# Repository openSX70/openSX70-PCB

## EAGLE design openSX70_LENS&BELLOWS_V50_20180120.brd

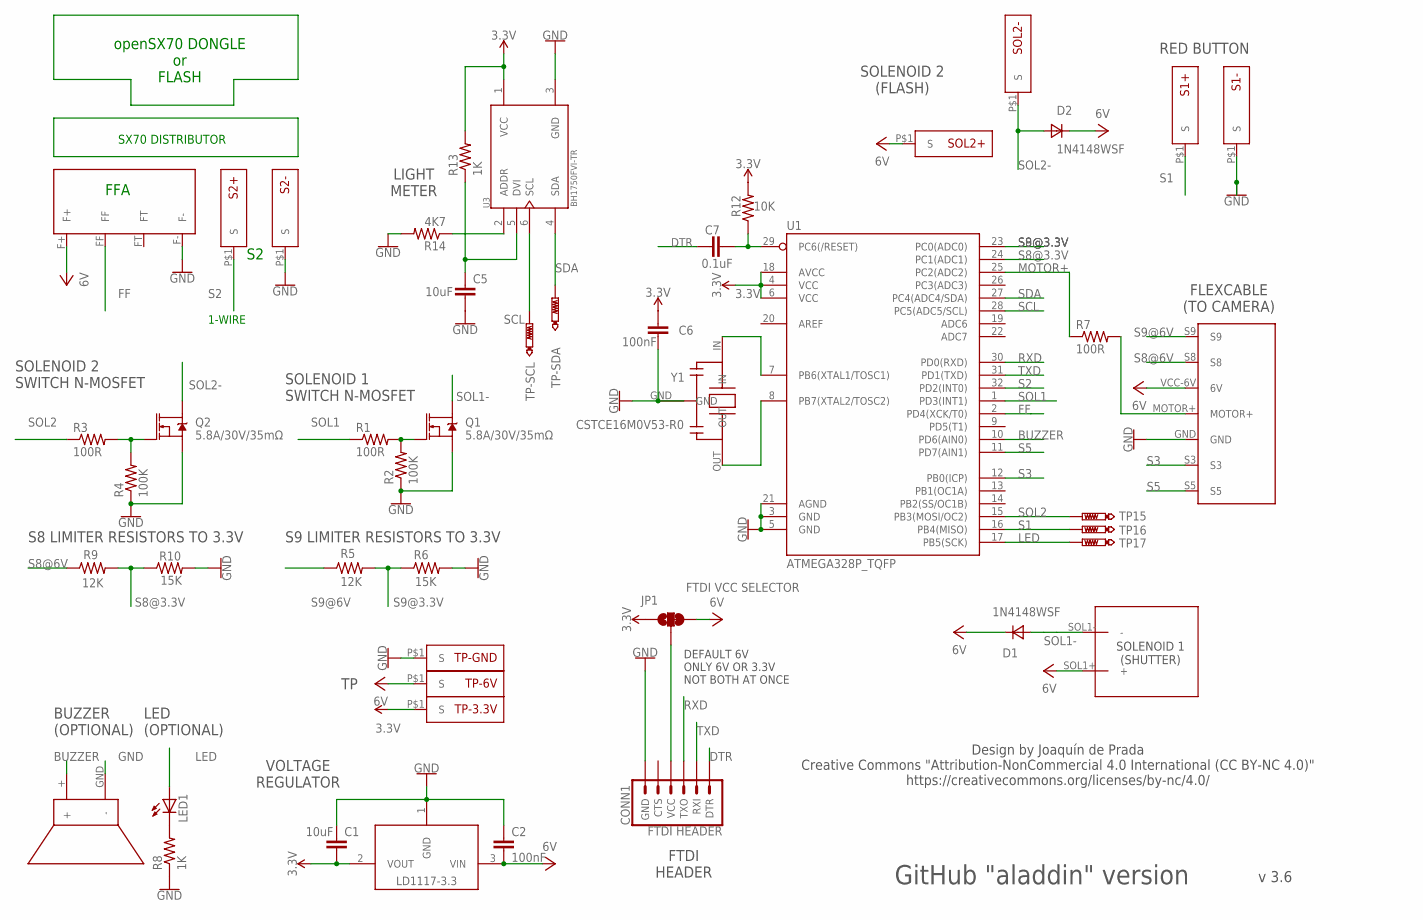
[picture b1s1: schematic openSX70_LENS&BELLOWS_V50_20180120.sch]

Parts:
BUZZ1: CSET8-5G; CSET8-5G_PACKAGE
C1, C5: 10uF; 0603
C2, C6: 100nF; C0603K
C7: 0.1uF; 0603
CONN1: FTDI HEADER; 1X06
D1, D2: 1N4148WSF; SOD323
JP1: FTDI VCC SELECTOR; SMT-JUMPER_3_1-NC_TRACE_SILK
LD11173.3V: LD1117 3.3V; SOT223
LED1: LEDCHIPLED_0805; CHIPLED_0805
Q1, Q2: 5.8A/30V/35mΩ; SOT23-3
R1, R3, R7: 100R; R0603
R2, R4: 100K; R0603
R5, R9: 12K; R0603
R6, R10: 15K; R0603
R8, R13: 1K; R0603
R12: 10K; R0603
R14: 4K7; R0603
S1+, S1-, S2+, S2-: SX70-S-PAD-NEW; SX70-S-PAD2
SOL1: SX70-SOLENOID1-2PADS; SX70-SOLENOID1-2
SOL2+, SOL2-: SX70-S-PAD-NEW; SX70-S-PAD2
TP15, TP16, TP17: PTR1TP08R; TP08R
TP-3.3V, TP-6V: SX70-S-PAD-NEW; SX70-S-PAD2
TP-GND: SX70-S-PAD-NEW; SX70-S-PAD2
TP-SCL: PTR1TP08R; TP08R
TP-SDA: PTR1TP08R; TP08R
U1: ATMEGA328P_TQFP; TQFP32-08
U3: BH1750FVI-TR; SOTFL50P300X75-6N
U$1: SX70-7-PAD
U$2: FFA; FFA-PAD-PACKAGE
Y1: CSTCE16M0V53-R0; CFP95P160X100-3N

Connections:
3.3V: C1.2, C6.1, JP1.1, LD11173.3V.2 (VOUT), R12.2, R13.2, TP-3.3V.P$1, U1.4 (VCC), U1.6 (VCC), U1.18 (AVCC), U3.1 (VCC)
6V: C2.2, D1.1 (C), D2.1 (C), JP1.3, LD11173.3V.3 (VIN), SOL1.SOL1+ (+), SOL2+.P$1, TP-6V.P$1, U$1.VCC-6V (6V), U$2.F+
BUZZER: BUZZ1.+, U1.10 (PD6(AIN0))
DTR: C7.1, CONN1.1 (DTR)
FF: U1.2 (PD4(XCK/T0)), U$2.FF
GND: BUZZ1.GND (-), C1.1, C2.1, C5.2, C6.2, CONN1.6 (GND), LD11173.3V.1 (GND), Q1.2 (S), Q2.2 (S), R2.1, R4.1, R6.2, R8.1, R10.2, R14.2, S1-.P$1, S2-.P$1, TP-GND.P$1, U1.3 (GND), U1.5 (GND), U1.21 (AGND), U3.3 (GND), U$1.GND, U$2.F-, Y1.GND
LED: LED1.A, TP17.TP, U1.17 (PB5(SCK))
MOTOR+: R7.1, U1.25 (PC2(ADC2))
MOTOR-HEADER: R7.2, U$1.MOTOR+
unnamed: Q1.1 (G), R1.2, R2.2
unnamed: C5.1, R13.1, U3.5 (DVI)
unnamed: Q2.1 (G), R3.2, R4.2
unnamed: U1.7 (PB6(XTAL1/TOSC1)), Y1.IN
unnamed: LED1.C, R8.2
unnamed: U1.8 (PB7(XTAL2/TOSC2)), Y1.OUT
unnamed: C7.2, R12.1, U1.29 (PC6(/RESET))
unnamed: R14.1, U3.2 (ADDR)
unnamed: CONN1.4 (VCC), JP1.2
RXD: CONN1.3 (TXO), U1.30 (PD0(RXD))
S1: S1+.P$1, TP16.TP, U1.16 (PB4(MISO))
S2: S2+.P$1, U1.32 (PD2(INT0))
S3: U1.12 (PB0(ICP)), U$1.S3
S5: U1.11 (PD7(AIN1)), U$1.S5
S8@3.3V: R9.2, R10.1, U1.24 (PC1(ADC1))
S8@6V: R9.1, U$1.S8
S9@3.3V: R5.2, R6.1, U1.23 (PC0(ADC0))
S9@6V: R5.1, U$1.S9
SCL: TP-SCL.TP, U1.28 (PC5(ADC5/SCL)), U3.6 (SCL)
SDA: TP-SDA.TP, U1.27 (PC4(ADC4/SDA)), U3.4 (SDA)
SOL1: R1.1, U1.1 (PD3(INT1))
SOL1-: D1.2 (A), Q1.3 (D), SOL1.SOL1- (-)
SOL2: R3.1, TP15.TP, U1.15 (PB3(MOSI/OC2))
SOL2-: D2.2 (A), Q2.3 (D), SOL2-.P$1
TXD: CONN1.2 (RXI), U1.31 (PD1(TXD))

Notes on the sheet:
1-WIRE
FFA
LIGHT METER
FLEXCABLE (TO CAMERA)
RED BUTTON
SOLENOID 1 (SHUTTER)
SOLENOID 2 (FLASH)
FTDI HEADER
VOLTAGE REGULATOR
BUZZER (OPTIONAL)
LED (OPTIONAL)
S8 LIMITER RESISTORS TO 3.3V
S9 LIMITER RESISTORS TO 3.3V
SOLENOID 2 SWITCH N-MOSFET
SOLENOID 1 SWITCH N-MOSFET
SX70 DISTRIBUTOR
openSX70 DONGLE or FLASH
v 3.6
Design by Joaquín de Prada Creative Commons "Attribution-NonCommercial 4.0 International (CC BY-NC 4.0)" https://creativecommons.org/licenses/by-nc/4.0/
GitHub "aladdin" version
DEFAULT 6V ONLY 6V OR 3.3V NOT BOTH AT ONCE

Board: 2 copper layers, 47 parts (7 on the bottom side), 34 nets, no tracks yet.

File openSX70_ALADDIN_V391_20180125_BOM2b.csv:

Qty,Value,Device,Package,Parts,Description,,
1,,LEDCHIPLED_0805,CHIPLED_0805,LED1,LED,,
1,0.1uF,0.1UF-0603-25V-(+80/-20%),0603,C7,0.1µF ceramic capacitors,,
2,100K,R-US_R0603,R0603,R2, R4,RESISTOR, American symbol,,
3,100R,R-US_R0603,R0603,R1, R3, R7,RESISTOR, American symbol,,
1,100nF,C-EUC0603,C0603,C6,CAPACITOR, European symbol,,
1,100nF,C-EUC0603K,C0603K,C2,CAPACITOR, European symbol,,
3,10K,R-US_R0603,R0603,R6, R10, R12,RESISTOR, American symbol,,
2,10uF,10UF-0603-6.3V-20%,0603,C1, C5,10.0µF ceramic capacitors,,
2,15K,R-US_R0603,R0603,R5, R9,RESISTOR, American symbol,,
2,1K,R-US_R0603,R0603,R8, R13,RESISTOR, American symbol,,
2,1N4148WSF,DSOD323,SOD323,D1, D2,DIODE,,
1,4K7,R-US_R0603,R0603,R14,RESISTOR, American symbol,,
2,5.8A/30V/35mO,MOSFET-NCH-AO3404A,SOT23-3,Q1, Q2,N-channel MOSFETs,,
1,ATMEGA328P_TQFP,ATMEGA328P_TQFP,TQFP32-08,U1,Popular 328P in QFP,,
1,BH1750FVI-TR,BH1750FVI-TR,SOTFL50P300X75-6N,U3,Light to Digital Ambient Light Sensor Digital O/P 1lux to 65535lux 6-Pin WSOF Embossed T/R,,
1,CSET8-5G,CSET8-5G,CSET8-5G_PACKAGE,BUZZ1,,,
1,CSTCE16M0V53-R0,CSTCE16M0V53-R0,CFP95P160X100-3N,Y1,Ceramic Resonator 16MHz ±0.5% (Tol) ±0.3% (Stability) 15pF 40Ohm 3-Pin CSMD T/R,,
1,FFA,SX70-FFA-PAD,FFA-PAD-PACKAGE,U$2,,,
1,FTDI VCC SELECTOR,JUMPER-SMT_3_1-NC_TRACE_SILK,SMT-JUMPER_3_1-NC_TRACE_SILK,JP1,Normally closed trace jumper (1 of 2 connections),,
1,GND,XF2L-0625-1,XF2L-0625-1,J1,OMRON FPC Connector,,
1,LD1117 2.5V,LD1117-3.3,SOT223,LD11172.5V,,,
5,PTR1TP08R,PTR1TP08R,TP08R,MISO, MOSI, SCK, SCL, SDA,TEST PIN,,

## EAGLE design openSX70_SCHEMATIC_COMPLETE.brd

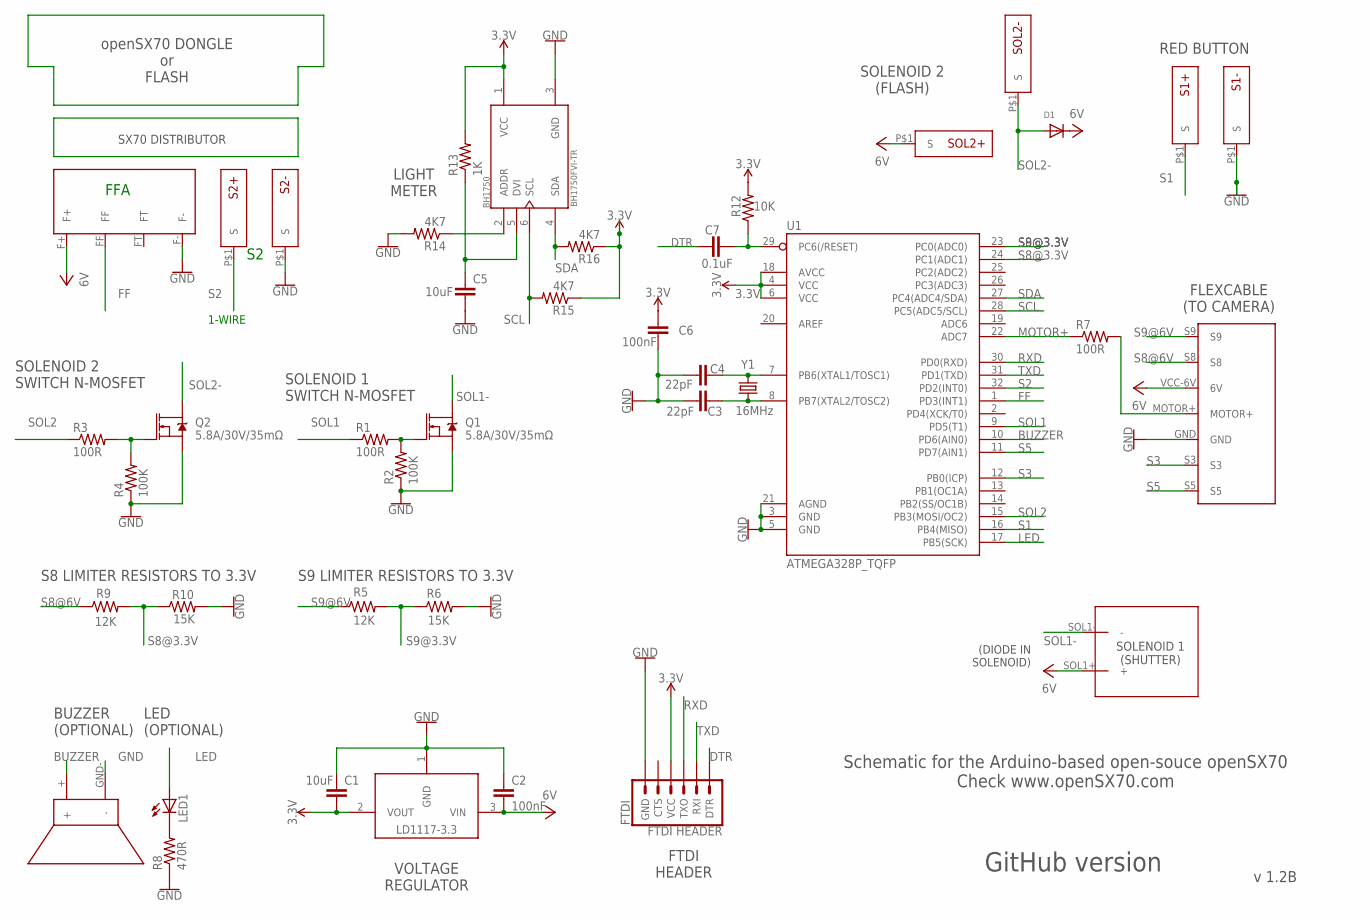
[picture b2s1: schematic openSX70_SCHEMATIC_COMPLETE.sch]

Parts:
BH1750: BH1750FVI-TR; SOTFL50P300X75-6N
BUZZER: CSET8-5G; CSET8-5G_PACKAGE
C1, C5: 10uF; 0603
C2: 100nF; C0603K
C3, C4: 22pF; 0603
C6: 100nF; C0805
C7: 0.1uF; 0603
D1: DIODESOD-523; SOD-523
FTDI: FTDI HEADER; 1X06
LD11173.3V: LD1117 3.3V; SOT223
LED1: LEDCHIPLED_0805; CHIPLED_0805
Q1, Q2: 5.8A/30V/35mΩ; SOT23-3
R1, R3, R7: 100R; R0603
R2, R4: 100K; R0603
R5, R9: 12K; R0603
R6, R10: 15K; R0603
R8: 470R; R0603
R12: 10K; R0603
R13: 1K; R0603
R14, R15, R16: 4K7; R0603
S1+, S1-, S2+, S2-: SX70-S-PAD-NEW; SX70-S-PAD2
SOL1: SX70-SOLENOID1-2PADS; SX70-SOLENOID1-2
SOL2+, SOL2-: SX70-S-PAD-NEW; SX70-S-PAD2
U1: ATMEGA328P_TQFP; TQFP32-08
U$1: SX70-7-PAD
U$2: SX70-FFA-PAD; FFA-PAD-PACKAGE
Y1: 16MHz; CRYSTAL-SMD-5X3.2-4PAD

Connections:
3.3V: BH1750.1 (VCC), C1.2, C6.1, FTDI.4 (VCC), LD11173.3V.2 (VOUT), R12.2, R13.2, R15.1, R16.1, U1.4 (VCC), U1.6 (VCC), U1.18 (AVCC)
6V: C2.2, D1.K (C), LD11173.3V.3 (VIN), SOL1.SOL1+ (+), SOL2+.P$1, U$1.VCC-6V (6V), U$2.F+
BUZZER: BUZZER.+, U1.10 (PD6(AIN0))
DTR: C7.1, FTDI.1 (DTR)
FF: U1.1 (PD3(INT1)), U$2.FF
GND: BH1750.3 (GND), BUZZER.GND- (-), C1.1, C2.1, C3.1, C4.1, C5.2, C6.2, FTDI.6 (GND), LD11173.3V.1 (GND), Q1.2 (S), Q2.2 (S), R2.1, R4.1, R6.2, R8.1, R10.2, R14.2, S1-.P$1, S2-.P$1, U1.3 (GND), U1.5 (GND), U1.21 (AGND), U$1.GND, U$2.F-
LED: LED1.A, U1.17 (PB5(SCK))
MOTOR+: R7.1, U1.22 (ADC7)
MOTOR-HEADER: R7.2, U$1.MOTOR+
unnamed: Q1.1 (G), R1.2, R2.2
unnamed: BH1750.5 (DVI), C5.1, R13.1
unnamed: Q2.1 (G), R3.2, R4.2
unnamed: C4.2, U1.7 (PB6(XTAL1/TOSC1)), Y1.3 (2)
unnamed: LED1.C, R8.2
unnamed: C3.2, U1.8 (PB7(XTAL2/TOSC2)), Y1.1
unnamed: C7.2, R12.1, U1.29 (PC6(/RESET))
unnamed: BH1750.2 (ADDR), R14.1
RXD: FTDI.3 (TXO), U1.30 (PD0(RXD))
S1: S1+.P$1, U1.16 (PB4(MISO))
S2: S2+.P$1, U1.32 (PD2(INT0))
S3: U1.12 (PB0(ICP)), U$1.S3
S5: U1.11 (PD7(AIN1)), U$1.S5
S8@3.3V: R9.2, R10.1, U1.24 (PC1(ADC1))
S8@6V: R9.1, U$1.S8
S9@3.3V: R5.2, R6.1, U1.23 (PC0(ADC0))
S9@6V: R5.1, U$1.S9
SCL: BH1750.6 (SCL), R15.2, U1.28 (PC5(ADC5/SCL))
SDA: BH1750.4 (SDA), R16.2, U1.27 (PC4(ADC4/SDA))
SOL1: R1.1, U1.9 (PD5(T1))
SOL1-: Q1.3 (D), SOL1.SOL1- (-)
SOL2: R3.1, U1.15 (PB3(MOSI/OC2))
SOL2-: D1.A, Q2.3 (D), SOL2-.P$1
TXD: FTDI.2 (RXI), U1.31 (PD1(TXD))

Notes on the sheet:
1-WIRE
(DIODE IN SOLENOID)
FFA
LIGHT METER
FLEXCABLE (TO CAMERA)
RED BUTTON
SOLENOID 1 (SHUTTER)
SOLENOID 2 (FLASH)
FTDI HEADER
VOLTAGE REGULATOR
BUZZER (OPTIONAL)
LED (OPTIONAL)
S8 LIMITER RESISTORS TO 3.3V
S9 LIMITER RESISTORS TO 3.3V
SOLENOID 2 SWITCH N-MOSFET
SOLENOID 1 SWITCH N-MOSFET
SX70 DISTRIBUTOR
openSX70 DONGLE or FLASH
v 1.2B
Schematic for the Arduino-based open-souce openSX70 Check www.openSX70.com
GitHub version

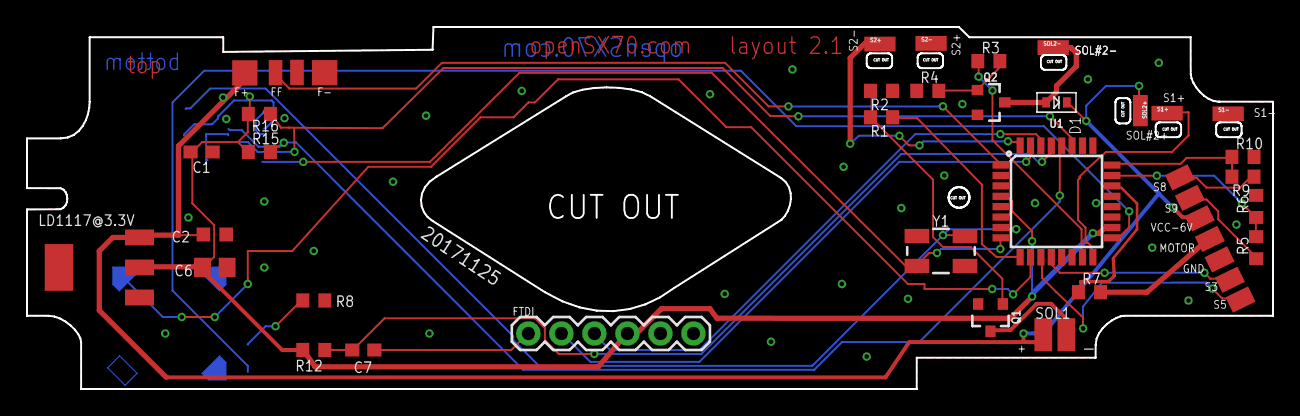
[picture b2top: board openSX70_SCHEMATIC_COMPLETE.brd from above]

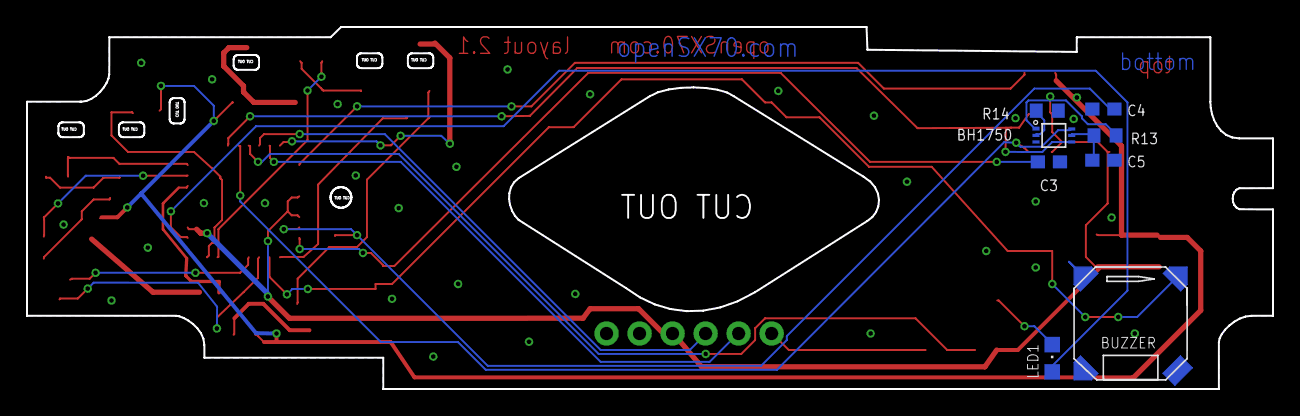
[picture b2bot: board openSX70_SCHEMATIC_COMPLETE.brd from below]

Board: 2 copper layers, 95.9 x 27.9 mm, 41 parts (8 on the bottom side), 33 nets.

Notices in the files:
parts and their libraries:
SparkFun-Capacitors: Licensing: Creative Commons ShareAlike 4.0 International - https://creativecommons.org/licenses/by-sa/4.0
